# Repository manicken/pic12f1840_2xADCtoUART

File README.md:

# pic12f1840_2xADCtoUART
8pin pic micro 2x ADC values to UART

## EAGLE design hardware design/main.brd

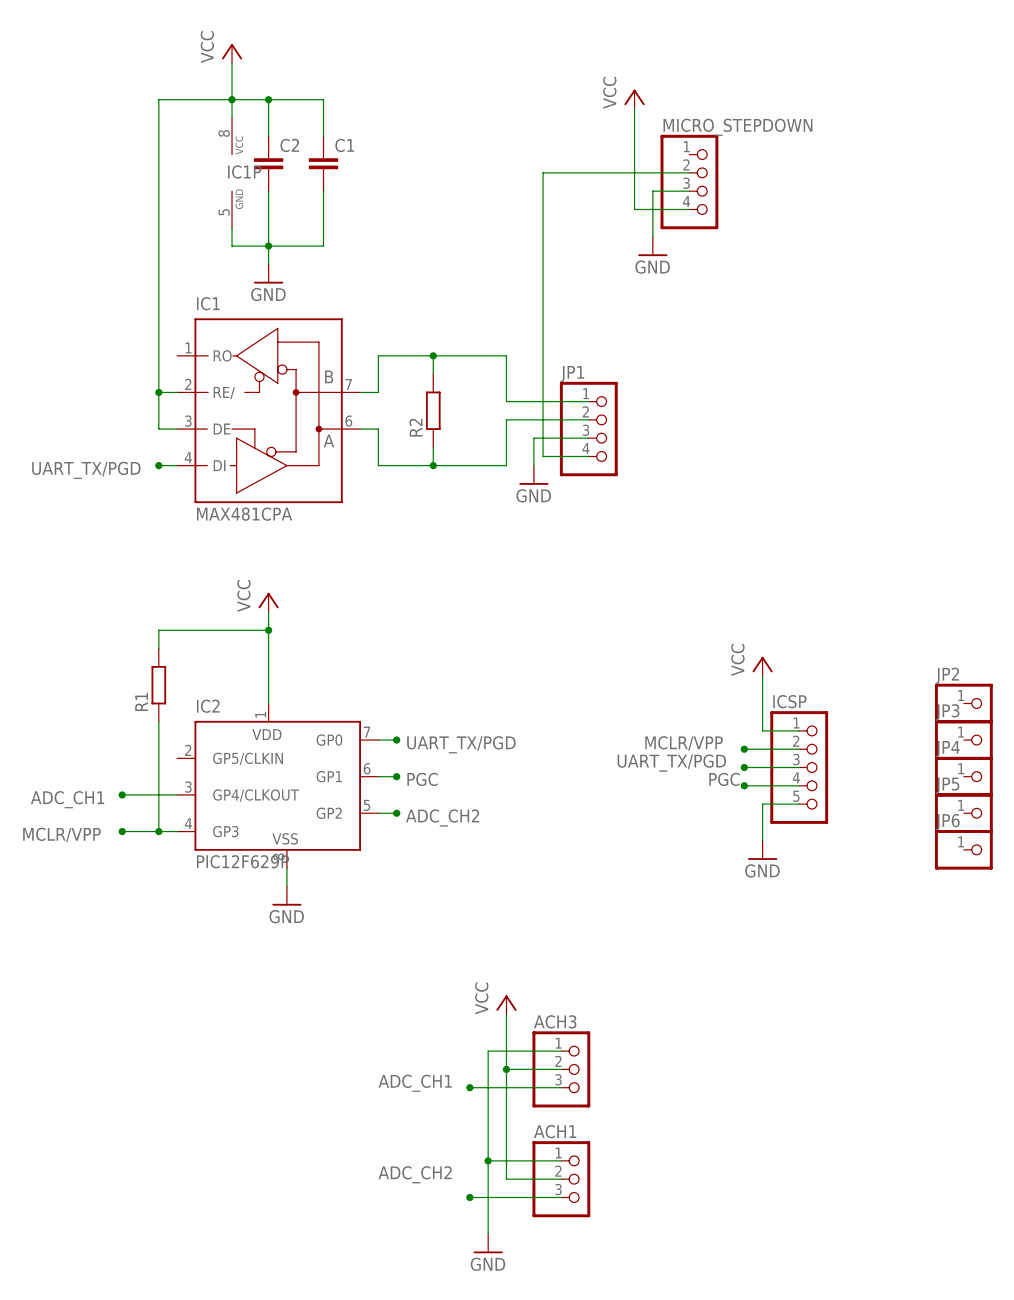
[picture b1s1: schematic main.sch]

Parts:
ACH1, ACH3: PINHD-1X3; 1X03
C1, C2: C-EUC0603; C0603
IC1: MAX481CPA; DIL08
IC2: PIC12F629P; DIL8
ICSP: PINHD-1X5; 1X05
JP1: PINHD-1X4; 1X04
JP2, JP3, JP4, JP5, JP6: PINHD-1X1; 1X01
MICRO_STEPDOWN: PINHD-1X4/90; 1X04/90
R1, R2: R-EU_R0603; R0603

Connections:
ADC_CH1: ACH3.3, IC2.3 (GP4/CLKOUT)
ADC_CH2: ACH1.3, IC2.5 (GP2)
GND: ACH1.1, ACH3.1, C1.2, C2.2, IC1.5 (GND), IC2.8 (VSS), ICSP.5, JP1.3, MICRO_STEPDOWN.3
MCLR/VPP: IC2.4 (GP3), ICSP.2, R1.1
unnamed: IC1.7 (B), JP1.1, R2.2
unnamed: IC1.6 (A), JP1.2, R2.1
unnamed: JP1.4, MICRO_STEPDOWN.2
PGC: IC2.6 (GP1), ICSP.4
UART_TX/PGD: IC1.4 (DI), IC2.7 (GP0), ICSP.3
VCC: ACH1.2, ACH3.2, C1.1, C2.1, IC1.2 (RE/), IC1.3 (DE), IC1.8 (VCC), IC2.1 (VDD), ICSP.1, MICRO_STEPDOWN.4, R1.2

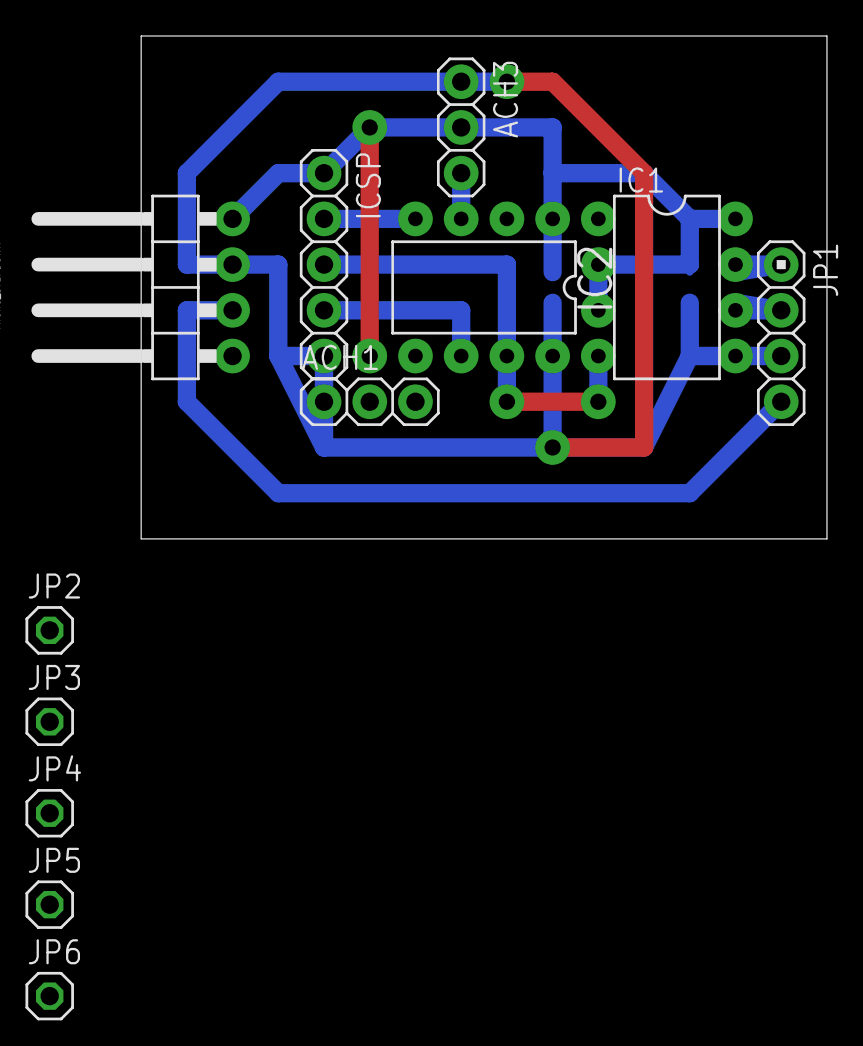
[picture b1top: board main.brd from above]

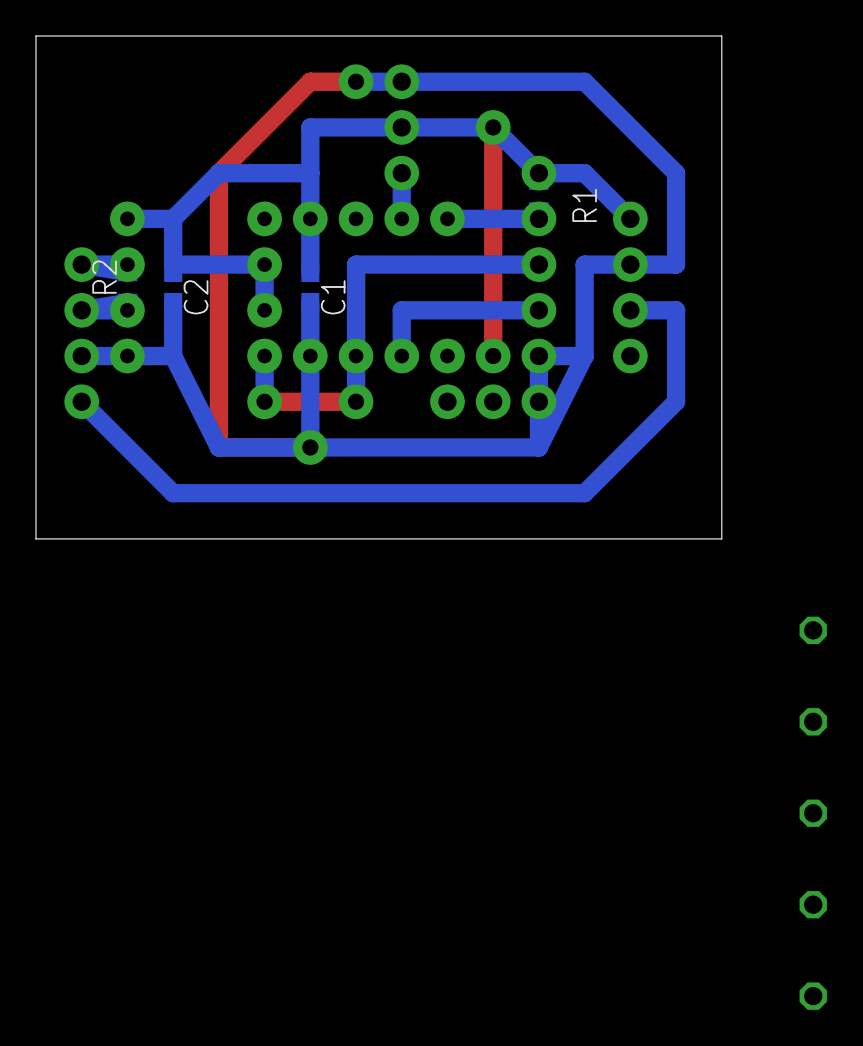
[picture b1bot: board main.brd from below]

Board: 2 copper layers, 38.1 x 27.9 mm, 16 parts (4 on the bottom side), 10 nets.

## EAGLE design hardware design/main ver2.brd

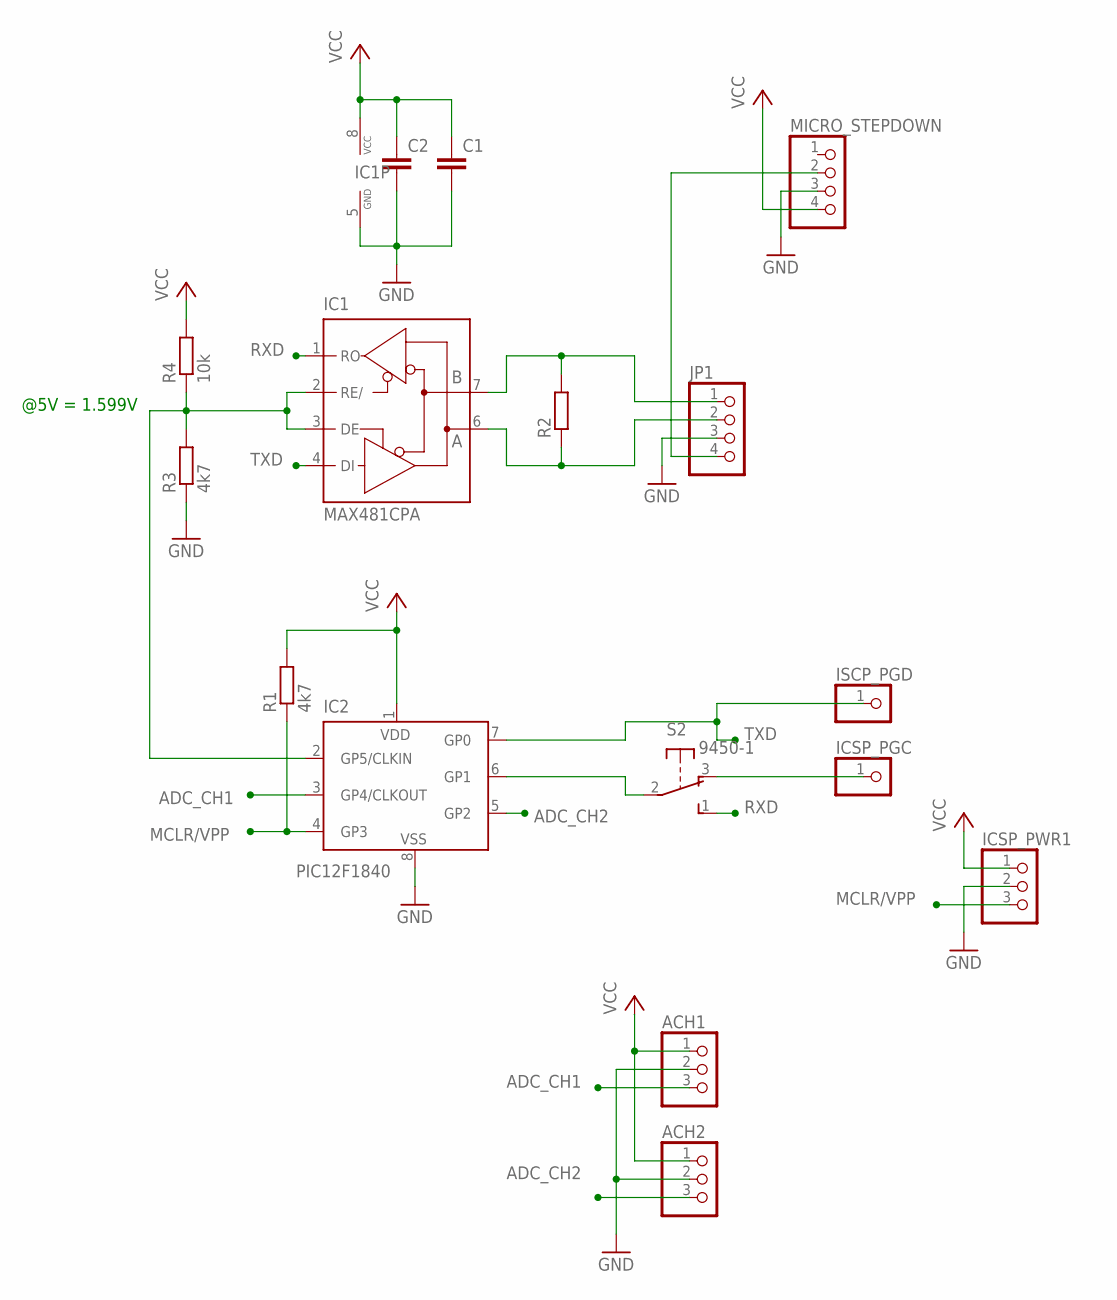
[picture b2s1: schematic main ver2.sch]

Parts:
ACH1, ACH2: PINHD-1X3; 1X03
C1, C2: C-EUC0603; C0603
IC1: MAX481CPA; DIL08
IC2: PIC12F1840; DIL8
ICSP_PGC: PINHD-1X1; 1X01
ICSP_PWR1: PINHD-1X3; 1X03
ISCP_PGD: PINHD-1X1; 1X01
JP1: PINHD-1X4; 1X04
MICRO_STEPDOWN: PINHD-1X4/90; 1X04/90
R1, R3: 4k7; R0603
R2: R-EU_R0603; R0603
R4: 10k; R0603
S2: 9450-1

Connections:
ADC_CH1: ACH1.3, IC2.3 (GP4/CLKOUT)
ADC_CH2: ACH2.3, IC2.5 (GP2)
GND: ACH1.2, ACH2.2, C1.2, C2.2, IC1.5 (GND), IC2.8 (VSS), ICSP_PWR1.2, JP1.3, MICRO_STEPDOWN.3, R3.1
MCLR/VPP: IC2.4 (GP3), ICSP_PWR1.3, R1.1
unnamed: IC1.7 (B), JP1.1, R2.2
unnamed: IC1.6 (A), JP1.2, R2.1
unnamed: JP1.4, MICRO_STEPDOWN.2
unnamed: IC1.2 (RE/), IC1.3 (DE), IC2.2 (GP5/CLKIN), R3.2, R4.1
unnamed: IC2.6 (GP1), S2.2
unnamed: ICSP_PGC.1, S2.3 (O)
RXD: IC1.1 (RO), S2.1 (S)
TXD: IC1.4 (DI), IC2.7 (GP0), ISCP_PGD.1
VCC: ACH1.1, ACH2.1, C1.1, C2.1, IC1.8 (VCC), IC2.1 (VDD), ICSP_PWR1.1, MICRO_STEPDOWN.4, R1.2, R4.2

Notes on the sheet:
@5V = 1.599V

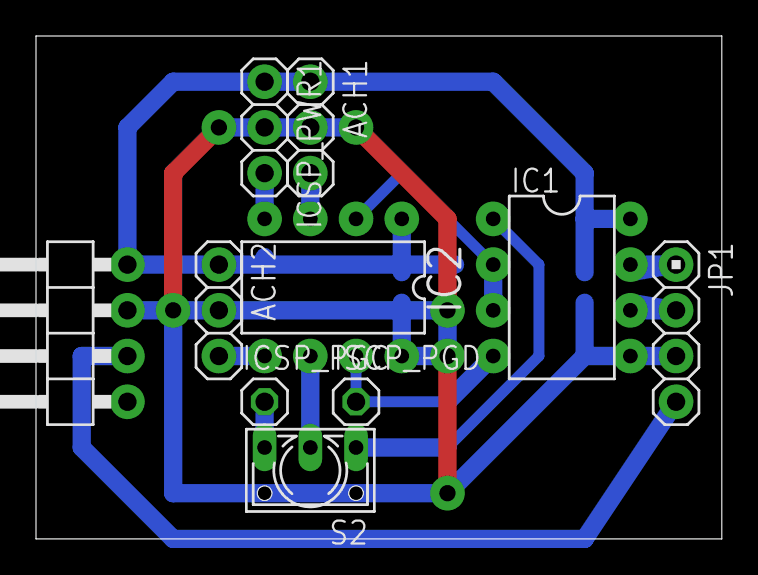
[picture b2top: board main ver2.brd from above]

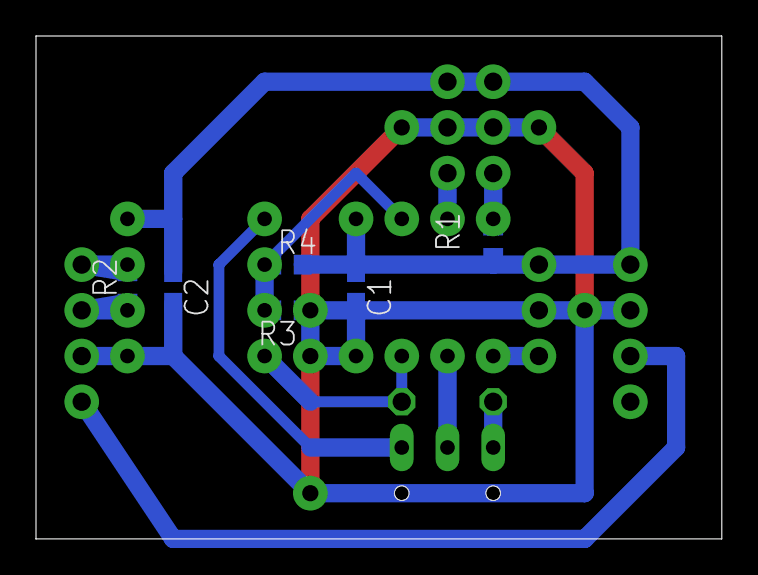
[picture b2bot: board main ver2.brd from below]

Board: 2 copper layers, 38.1 x 27.9 mm, 16 parts (6 on the bottom side), 13 nets.

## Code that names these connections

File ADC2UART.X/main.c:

// CONFIG1
#pragma config FOSC = INTOSC    // Oscillator Selection (INTOSC oscillator: I/O function on CLKIN pin)
#pragma config WDTE = OFF       // Watchdog Timer Enable (WDT disabled)
#pragma config PWRTE = ON       // Power-up Timer Enable (PWRT enabled)
#pragma config MCLRE = ON       // MCLR Pin Function Select (MCLR/VPP pin function is MCLR)
#pragma config CP = OFF         // Flash Program Memory Code Protection (Program memory code protection is disabled)
#pragma config CPD = OFF        // Data Memory Code Protection (Data memory code protection is disabled)
#pragma config BOREN = ON       // Brown-out Reset Enable (Brown-out Reset enabled)
#pragma config CLKOUTEN = OFF   // Clock Out Enable (CLKOUT function is disabled. I/O or oscillator function on the CLKOUT pin)
#pragma config IESO = OFF       // Internal/External Switchover (Internal/External Switchover mode is disabled)
#pragma config FCMEN = ON       // Fail-Safe Clock Monitor Enable (Fail-Safe Clock Monitor is enabled)

// CONFIG2
#pragma config WRT = OFF        // Flash Memory Self-Write Protection (Write protection off)
#pragma config PLLEN = OFF      // PLL Enable (4x PLL disabled)
#pragma config STVREN = ON      // Stack Overflow/Underflow Reset Enable (Stack Overflow or Underflow will cause a Reset)
#pragma config BORV = LO        // Brown-out Reset Voltage Selection (Brown-out Reset Voltage (Vbor), low trip point selected.)
#pragma config LVP = OFF        // Low-Voltage Programming Enable (High-voltage on MCLR/VPP must be used for programming)


#include <xc.h>
#include <stdint.h>

#define ADC_CH1 0x03 // AN3 @RA4 PIN3
#define ADC_CH2 0x02 // AN2 @RA2 PIN5
#define ADC_TEMP 0x1D // Temperature Indicator

#define ADC_CH1_VREF 0x01; // VREF @ 1.024V
#define ADC_CH2_VREF 0x02; // VREF @ 2.048V

void delay(uint16_t ms);

void UART_send_char(uint8_t data);
void UART_send_nah(uint8_t nibble); // sends nibble as ASCII HEX
void UART_send_2nah(uint8_t byte); // sends as 2 nibble ASCII HEX
void UART_send_uint16_4dec(uint16_t val);

uint8_t adc_ch1_val_msb = 0;
uint8_t adc_ch1_val_lsb = 0;
uint8_t adc_ch2_val_msb = 0;
uint8_t adc_ch2_val_lsb = 0;

uint8_t adc_temp_val_msb = 0; // temperature value
uint8_t adc_temp_val_lsb = 0; // temperature value

void main() {
    OSCCON = 0x73; // PLL off, 8MHz int osc
    while (OSCSTATbits.HFIOFS == 0) {}
    
    PORTA = 0x00;
    LATA = 0x00;
    TRISA = 0xFF;
    TRISAbits.TRISA0 = 0; // UART TX pin
    
    LATAbits.LATA5 = 1; // MAX487 transmit mode
    TRISAbits.TRISA5 = 0; // MAX487 mode pin as output
    
    TXSTA = 0x84;
    RCSTA = 0x80;
    BAUDCON = 0x00;
    
    TXSTAbits.BRGH = 1;
    BAUDCONbits.BRG16 = 1;
    
    SPBRG = 0x67; // 103dec
    
    TXSTAbits.TXEN = 1;
    
    // setup 1mS delay timer
    OPTION_REGbits.TMR0CS = 0; //internal instruction cycle clock
    OPTION_REGbits.PSA = 0; //prescaler is to timer 0 module
    OPTION_REGbits.PS = 0x2; // prescaler is 8 which gives @ 250 timer clocks => 1mS
    
    // setup ADC
    ADCON0 = 0x00; // reset and disable ADC
    ADCON1 = (0x80 | 0x03); // size most significant bits of ADRESH are set to '0', VREF -> internal FVR
    ADCON1bits.ADCS = 0x05; // Fosc/16
    ADCON0bits.ADON = 1;
    
    FVRCON = 0xF0; // FVR enabled, temperature indicator enabled low range, both VREF outputs off
    delay(10); // 10mS
    
    while (1) {
        
        FVRCONbits.ADFVR = ADC_CH1_VREF;
        ADCON0bits.CHS = ADC_CH1;
        delay(1); // 1mS
        ADCON0bits.ADGO = 1; // starts conversion
        while (ADCON0bits.ADGO == 1) {} // wait for conversion to complete
        adc_ch1_val_msb = ADRESH;
        adc_ch1_val_lsb = ADRESL;
        
        FVRCONbits.ADFVR = ADC_CH2_VREF;
        ADCON0bits.CHS = ADC_CH2;
        delay(1); // 1mS
        ADCON0bits.ADGO = 1; // starts conversion
        while (ADCON0bits.ADGO == 1) {} // wait for conversion to complete
        adc_ch2_val_msb = ADRESH;
        adc_ch2_val_lsb = ADRESL;
        
        /* temp sensor don't work
        ADCON0bits.CHS = 0x1F; // 1F is FVR buffer output
        delay(1); // 1mS
        ADCON0bits.ADGO = 1; // starts conversion
        while (ADCON0bits.ADGO == 1) {} // wait for conversion to complete
        adc_temp_val_msb = ADRESH;
        adc_temp_val_lsb = ADRESL;
        */
        
        UART_send_char('@'); // start of message
        UART_send_char('S'); // slave response
        UART_send_char('P'); // unique id "Pressure"
        UART_send_char('S'); // unique id "Sensor"
        /*UART_send_nah(adc_ch1_val_msb);
        UART_send_2nah(adc_ch1_val_lsb);
        UART_send_char(' '); // space for easier debug read
        UART_send_nah(adc_ch2_val_msb);
        UART_send_2nah(adc_ch2_val_lsb);
        */
        UART_send_char(' '); // space for easier debug read
        UART_send_uint16_4dec(adc_ch1_val_msb * 256 + adc_ch1_val_lsb); // is in 1mV step
        UART_send_char(' '); // space for easier debug read
        UART_send_uint16_4dec((adc_ch2_val_msb * 256 + adc_ch2_val_lsb)*2); // *2 as each value represents 2mV
        /* temp sensor don't work
        UART_send_char(' '); // space for easier debug read
        UART_send_nah(adc_temp_val_msb);
        UART_send_2nah(adc_temp_val_lsb);
         */
        
        UART_send_char(0x0D); // end of message
        UART_send_char(0x0A); // end of message
        
        delay(1000);
        
    }
}

void delay(uint16_t ms) {
    
    while (ms != 0) {
        INTCONbits.TMR0IF = 0;
        TMR0 = 0x05; // gives 1mS at 8 prescaler @ fosc 8MHz
        asm("NOP");
        while (INTCONbits.TMR0IF == 0) {}
        ms--;
    }
}

void UART_send_char(uint8_t data) {
    TXREG = data;
    asm("NOP");
    while (TXSTAbits.TRMT == 0) { };
}

void UART_send_nah(uint8_t nibble) {
    nibble &= 0x0F;
    if (nibble < 10) UART_send_char(nibble + 0x30);
    else UART_send_char(nibble + 0x37);
}

void UART_send_2nah(uint8_t byte) { // sends as 2 nibble ASCII HEX
    
    // send_nah:s have nibble &= 0x0F; internally
    UART_send_nah(byte >> 4);
    UART_send_nah(byte);
}

void UART_send_uint16_4dec(uint16_t val) {
    uint8_t toSend = val / 1000;
    val = val % 1000;
    UART_send_char(toSend + 0x30);
    toSend = val / 100;
    val = val % 100;
    UART_send_char(toSend + 0x30);
    toSend = val / 10;
    val = val % 10;
    UART_send_char(toSend + 0x30);
    toSend = val;
    UART_send_char(toSend + 0x30);
}

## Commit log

2021-07-08 first release
2021-07-16 second
